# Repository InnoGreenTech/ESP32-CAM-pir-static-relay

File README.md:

ESP_CAM with Pir sensor, photo resistor and static relay.
========================================================

Description:
------------

This is a camera built around a ESP32-CAM. It allow to stream RTSP stream for your Video station like Synology for exemple.
It have two sensors, a Pir sensor to detect mouvement and a photo-resistor to detect luminosity and control integrate flash LED.
There is also a static relay to swith on a light or other actuators. It integrates a power supply. 

[*You can found more information on my web site on this page*](http://innogreentech.fr/en/connected-objects/camera/31-surveillance-camera-esp32-cam-with-pir-sensor-2)

[*I have used the great library of Kevin Hester-Chow*] https://github.com/geeksville/Micro-RTSP/blob/master/README.md

I share also the drawing and the pcb in this repository.

Contributing:
-------------

Fork it
Create your feature branch (git checkout -b my-new-feature)
Commit your changes (git commit -am 'Add some feature')
Push to the branch (git push origin my-new-feature)
Create new Pull Request

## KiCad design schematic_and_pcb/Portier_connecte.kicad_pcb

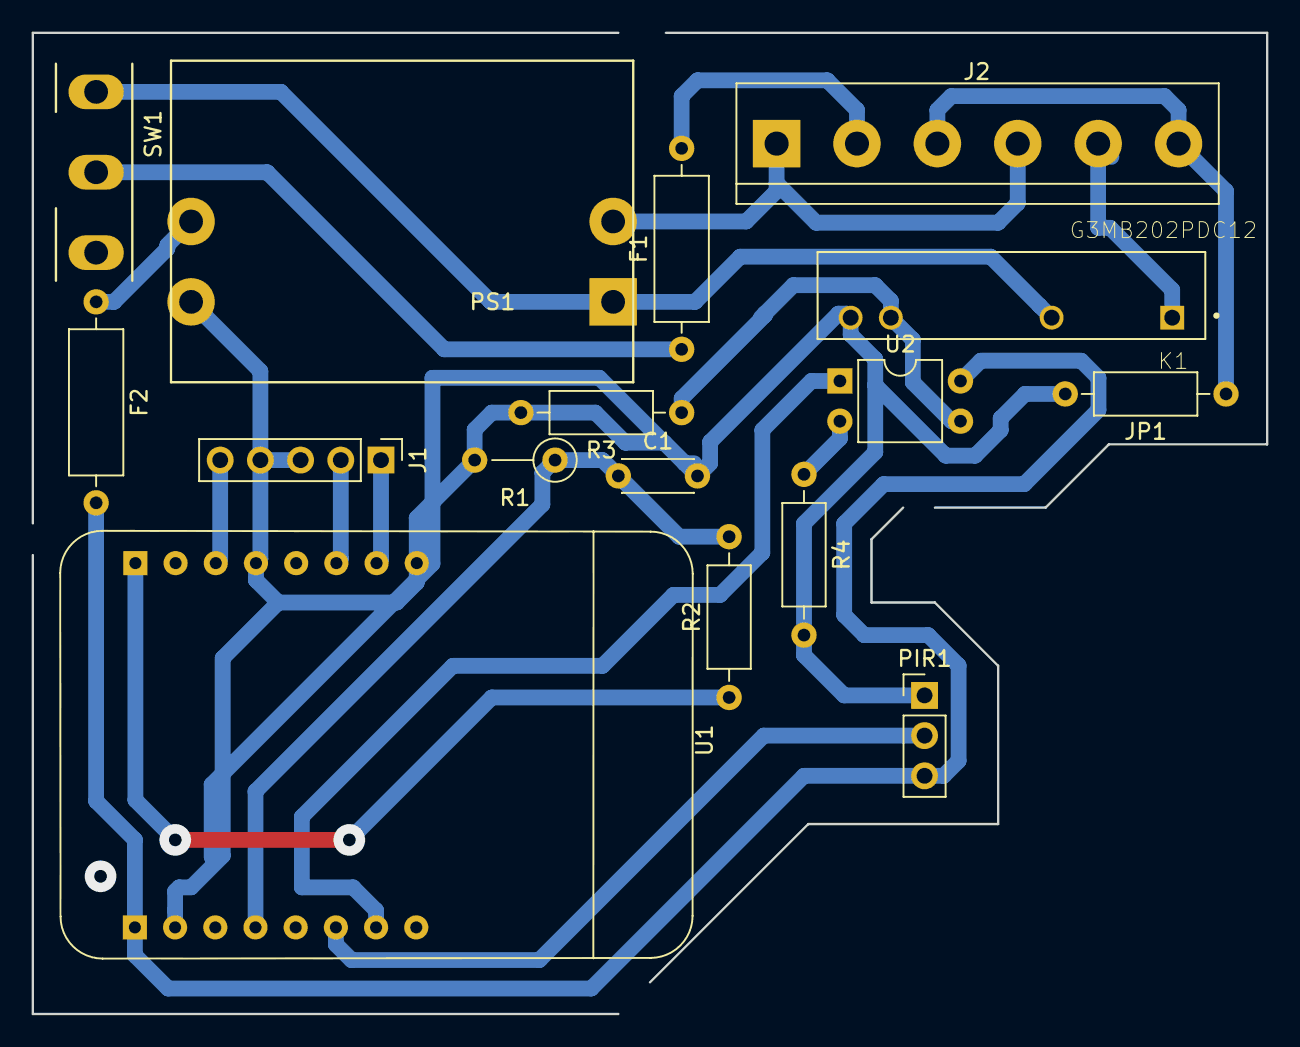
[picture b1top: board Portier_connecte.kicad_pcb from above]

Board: 2 copper layers, 78.0 x 62.0 mm, 16 parts (0 on the bottom side), 18 nets.

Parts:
C1: C; C_Disc_D4.3mm_W1.9mm_P5.00mm
F1, F2: Fuse; R_Axial_DIN0309_L9.0mm_D3.2mm_P12.70mm_Horizontal
J1: Conn_01x05_Male; PinHeader_1x05_P2.54mm_Vertical
J2: Screw_Terminal_01x06; TerminalBlock_bornier-6_P5.08mm
JP1: Jumper_NO_Small; R_Axial_DIN0207_L6.3mm_D2.5mm_P10.16mm_Horizontal
K1: G3MB202PDC12; RELAY_G3MB202PDC12
PIR1: PIR_Motion_Sensor; PinHeader_1x03_P2.54mm_Vertical
PS1: IRM-02-5; Converter_ACDC_YS100000590
R1: R_PHOTO; R_Axial_DIN0207_L6.3mm_D2.5mm_P5.08mm_Vertical
R2: 5k; R_Axial_DIN0207_L6.3mm_D2.5mm_P10.16mm_Horizontal
R3, R4: 220; R_Axial_DIN0207_L6.3mm_D2.5mm_P10.16mm_Horizontal
SW1: SW_DPDT_x2; SW_P5_Angled
U1: ESP32-CAM
U2: PC817; DIP-4_W7.62mm

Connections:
+3V3: R2.1, U1.8
+5V: F2.2, PIR1.3, U1.9, U2.4
Earth: J2.3, J2.6, JP1.1
GND: C1.2, J1.3, J1.4, JP1.2, K1.4, PIR1.1, PS1.4, R1.2, R3.2, R4.2, U1.1, U1.5, U1.10
unnamed: C1.1, R1.1, R2.2, U1.12
unnamed: F1.1, SW1.2
unnamed: F1.2, J2.2
unnamed: F2.1, PS1.3
unnamed: J1.1, U1.2
unnamed: J1.2, U1.3
unnamed: J1.5, U1.6
unnamed: J2.1, J2.4, PS1.2
unnamed: J2.5, K1.1
unnamed: K1.2, PS1.1, SW1.1
unnamed: K1.3, R3.1, U2.3
unnamed: PIR1.2, U1.14
unnamed: R4.1, U2.2
unnamed: U1.15, U2.1

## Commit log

2020-01-23 Start repository of camera
2020-01-26 update files
2020-05-21 update read file
